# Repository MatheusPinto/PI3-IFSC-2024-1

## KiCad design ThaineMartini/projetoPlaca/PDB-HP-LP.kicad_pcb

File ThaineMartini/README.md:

# <p align="center"> Comandos, Aquisição e Armazenamento de dados de uma bancada de teste de um sistema de energia híbrido para drone </p>

<p class="text-info recuo" align="justify">
O mercado atual de drones, são raras as opções que possuem autonomia de voo maior que 50 minutos, fator esse que pode dificultar ou mesmo inviabilizar a realização de algumas missões. A marca mais conhecida do mercado (DJI) possui apenas uma opção comercial que promete atuar em uma margem maior de tempo que o limiar mencionado. Essa condição existe por conta das limitações de densidade energética dos armazenadores de energia disponíveis no mercado: baterias. Nesse contexto, uma opção viável para aumentar a autonomia consiste na utilização de conjuntos híbridos que podem ser embarcados na aeronave, utilizando um motor à combustão como parte do sistema de geração de energia elétrica.
</p>
<p class="text-info recuo"align="justify">
Para implementar esse conjunto híbrido no drone, uma solução é importar sistemas pré-fabricados de geração de energia de outros países, como a China. Contudo a hipotética fabricação e nacionalização desse subsistema é uma solução interessante, haja vista o potencial de diminuição de custos, possibilidade de personalização da máquina e ausência dos trâmites de importação.
</p>

<p class="text-info recuo"align="justify">
Para realizar esse projeto, foi desenvolvida uma bancada de testes pelo laboratório de drones do Instituto Federal de Ciência e Tecnologia de Santa Catarina (IFSC). O dispositivo consiste em um motor a combustão interna (MCI) acoplado a um motor BrushLess Direct Current (BLDC), que funciona como gerador de energia, e um retificador trifásico conectado à saída do gerador. Nessa configuração, o acelerador do motor à combustão possui um atuador eletromecânico (servo) que pode ser acionado eletronicamente por um sistema microcontrolado, que deve ajustar automaticamente e em tempo real a posição do acelerador conforme a energia demandada na saída o gerador trifásico (BLDC). Um dos principais desafios dessa simulação é desenvolver um sistema eletrônico de monitoramento e controle que mantenha a tensão constante mesmo com a variação da carga. Com o objetivo de desenvolver esse sistema de controle, é necessário projetar e confeccionar uma placa auxiliar que condiciona os sinais aferidos no sistema para um microcontrolador onde são tratados e armazenados em um log. Essa placa será desenvolvida no projeto integrador 3 e será detalhada a seguir.
</p>

<p class="text-info recuo"align="justify">
Esse projeto integrador deve cumprir os seguintes requisitos, aferir e condicionar os sinais de RPM, temperatura do motor a combustão interna (MCI), corrente e tensão no barramento CC (pós-retificador) do sistema. Deve gerar dois sinais de pulse width modulation (PWM), um para o servo motor que acelera o MCI e outro para o driver que movimenta o BLDC para dar partida no motor. Esta placa também deve possuir dois conversores um de 12V e outro de 5V para a alimentação de payload e periféricos do drone. Assim como tem que gerar um arquivo de dados que contenha todos os sinais que foram monitorados. Na Figura 1, está delineado em formato de diagrama o projeto da PCI.
</p>
<div align="center">
Figura 1 - Diagrama do hardware

<figcaption>Fonte: Acervo pessoal</figcaption>
</div>

#### Cronograma idealizado 
<p> 12/03 - Cronograma </p>
<p> 20/03 - Levantamento dos componentes de projeto e pré requisitos </p>
<p> 27/03 - Levantamento dos componentes de projeto e pré requisitos </p>
<p> 03/04 - Esquemático da placa </p>
<p> 10/04 - Esquemático da placa </p>
<p> 17/04 - Layout da placa </p>
<p> 24/04 - Layout da placa </p>
<p> 08/05 - Fabricação da placa, documentação e programação do micro </p>
<p> 15/05 - Fabricação da placa, documentação e programação do micro </p>
<p> 22/05 - 1° TESTE e levantamento de log para análise </p>
<p> 29/05 - Ajustes </p>
<p> 05/06 - 2° TESTE e levantamento de log para análise </p>
<p> 12/06 - Ajustes </p>
<p> 19/06 - Apresentação </p>

## Desenvolvimento

### Componentes
<p> Os componentes foram selecionados de acordo com a disponibilidade no laboratório e com os requisitos o projeto </p>
<p> Servo motor: MG995, a aplicação necessita de um servo robusto e esse componente tem disponível no laboratório </p>
<p> UControlador: F280025C da Texas Instruments, um microcontrolador que aguenta o sistema de controle que será aplicado futuramente </p>
<p> Sensor de corrente: ACS758 150B, o máximo de corrente que o sensor terá que medir é de 80A, o sensor escolhido mede até 150A e tem disponivel no laboratório </p>
<p> Conversor CC/CC 48V - 5V: THL15-4811WL, robusto suficiente para aguentar os picos de tensão (até 60V) e tem disponivel no laboratório </p>
<p> Conversor CC/CC 48V - 12V: EC5SBW-48S12, robusto suficiente para aguentar os picos de tensão (até 60V) e tem disponivel no laboratório </p>
<p> Sensor de temperatura: NTC 33950 100k, o sensor deve medir pelo menos de 10 C até 200 C, o sensor escolhido mede de -4 a 270 C </p>
<p> Amplificador Opercional: TLV 9044 DIR, escolhido pela disponibilidade no laboratório </p>
<p> Regulador de Tensão: LM 1117 </p>

### Projeto
<p align="justify"> O projeto foi realizado de acordo com diagrama de blocos demonstrado anteriormente</p>

#### Leitura da corrente

<p align="justify">O circuito utilizado para a leitura da corrento envolve o sensor (ACS 758B), o condicionamento de sinal e um filtro ativo passa-baixa (Sallen-Key). Para a adequar os niveis de tensão foi utilizado um circuito subtrator, descrito abaixo </p>

<picture>
 
</picture>

<p align="justify">Para a tensão V1 maxima, levamos em consideração que quando a corrente é nula a tensão de saída do ACS vai ser Vcc/2 = 1.65.</p>
<p align="justify">Para a tensão V1 minima, levamos em consideração que quando a corrente é maxima a tensão de saída do ACS vai ser (Vcc/2) + (Corrente maxima * sensibilidade do sensor), a sensibilidade do sensor pelo datasheet é 13*10^-3 e a corrente  maxima prevista é 100 A (com uma certa sobra por precaução), com isso temos V2 = 2.95 </p>
<p align="justify">Para V2 é utilizado um divisor resistivo para conseguir a tensão de 1.5V (R1 = 1.2k ohm e R2=1k ohm).  </p>

<picture>
 
</picture>

#### Leitura da tensão 
<p align="justify"> Para a leitura da Tensão foi usado um divisor resistivo de tensão juntamente com um filtro Sallen-Key de segunda ordem (passa-baixa) para a diminuição de ruido na leitura do sinal. Para calcular o divisor resistivo foi assumindo que R1 = 56560 ohm (dividido em dois resistores um de 56k ohm e outro e 560 ohm), R2=3k3 ohm e com uma tensão maxima de 60V. Para o calculo do filtro Sallen-Key, foi previsto pelos professores do laboratori de dornes uma frequência de corte de 723 Hz para o filtro, para a definição dos capacitores e resistores foi utilizada a formula fc = 1/(2*pi*sqrt(R1*C1*R2*C2)) onde ao definir C1 e C2 com 100 nF, temos R1 e R2 de 2k2 ohm. O esquemático é mostrado na figura abaixo. </p>

<picture>
 
</picture>

### Esquemático 
<p align="justify">Através do software KiCad e com os requisitos levantados anteriormente foi realizado a implementação do esquemático (pdf com o esquemático completo na pasta do projeto), que é composto por 5 Blocos principais: </p>
<p> - Alimentação: O bloco de alimentação é formado pela conexão da Bateria de 12S (aproximadamente 48V) e a conexão do Gerador Elétrico</p>
<p> - Potência: Possui dois conversores THL15-4811WL (para 5V) e o EC5SBW-48S12 (para 12V), com o circuito sugerido na folha de dados</p>
<p> - Conexões: São as conexões que a placa possui com o meio esterno, primeramente o 4 conectores XT60 que são usados para a conectar a carga (para testes inicias uma carga resistiva), 3 conectores JST-XH de duas vias, um para a alimentação da bomba que auxilia no resfriamento o motor, outro para aferir a temperatura e por último para a ignição do motor, 6 conectores JST-XH de 3 vias sendo, para o esc que vai acionar o BLDC para dar a partida no motor a combustão, para o servo motor que auxilia no controle, um que recebe um pulso da controladora de voo para o acionamento remoto do motor, e dois reservas caso venha a precisar no futuro, alem desses conectores temos nesse bloco um optacoplador para proteção do circuito com o sinal que vem do tacomêtro, um jumper para a alimentação do F280025C caso precise debugar o circuito no computador, um modulo para leitura do cartão SD e dois leds para informações. Para a comunicação com a controladora de voo foi prevista duas conexões, uma por JST-XH  e uma por JST-GH, para conseguir utilizar os dois tipos de controlaora disponiveis no laboratório (cube orange e pixhalk)</p>
<p> - Condicionamento do Sinal: Contendo dois sinais que precisam ser ajustados para a leitura no F280025C a tensão que passa por um divisor resistivo para diminuir a tensão, um buffer e um filtro Sallen-Key e a corrente que após passar por um sensor de efeito hall (ACS758) passa por um buffer, um circuito somador para amplificar a tensão fornecida pelo sensor e um filtro sallen-key, o detalhemento desses dois circuitos está fornecido na folha de calculos.</p>

### Layout
<p>O layout seguiu os seguintes requisitos:</p>
  <p>- Deixar todos os componentes na parte superior da placa assim como os pontos de medição de tensão</p>
  <p>- A parte de potência separada e com menor interatividade com o resto da placa</p>
  <p>- Conectores na borda da placa </p>
  <p>- Malha de potência no barramento (no bloco de alimentação) </p>
  <p align="justify">Os requisitos foram pensados para evitar ruídos indesejados, evitar que a placa sobreaqueça, melhor conexão dos perifericos e para que acaso haja algum problema no futuro seja fácil de encontrar o que está gerando.</p>
### Programação

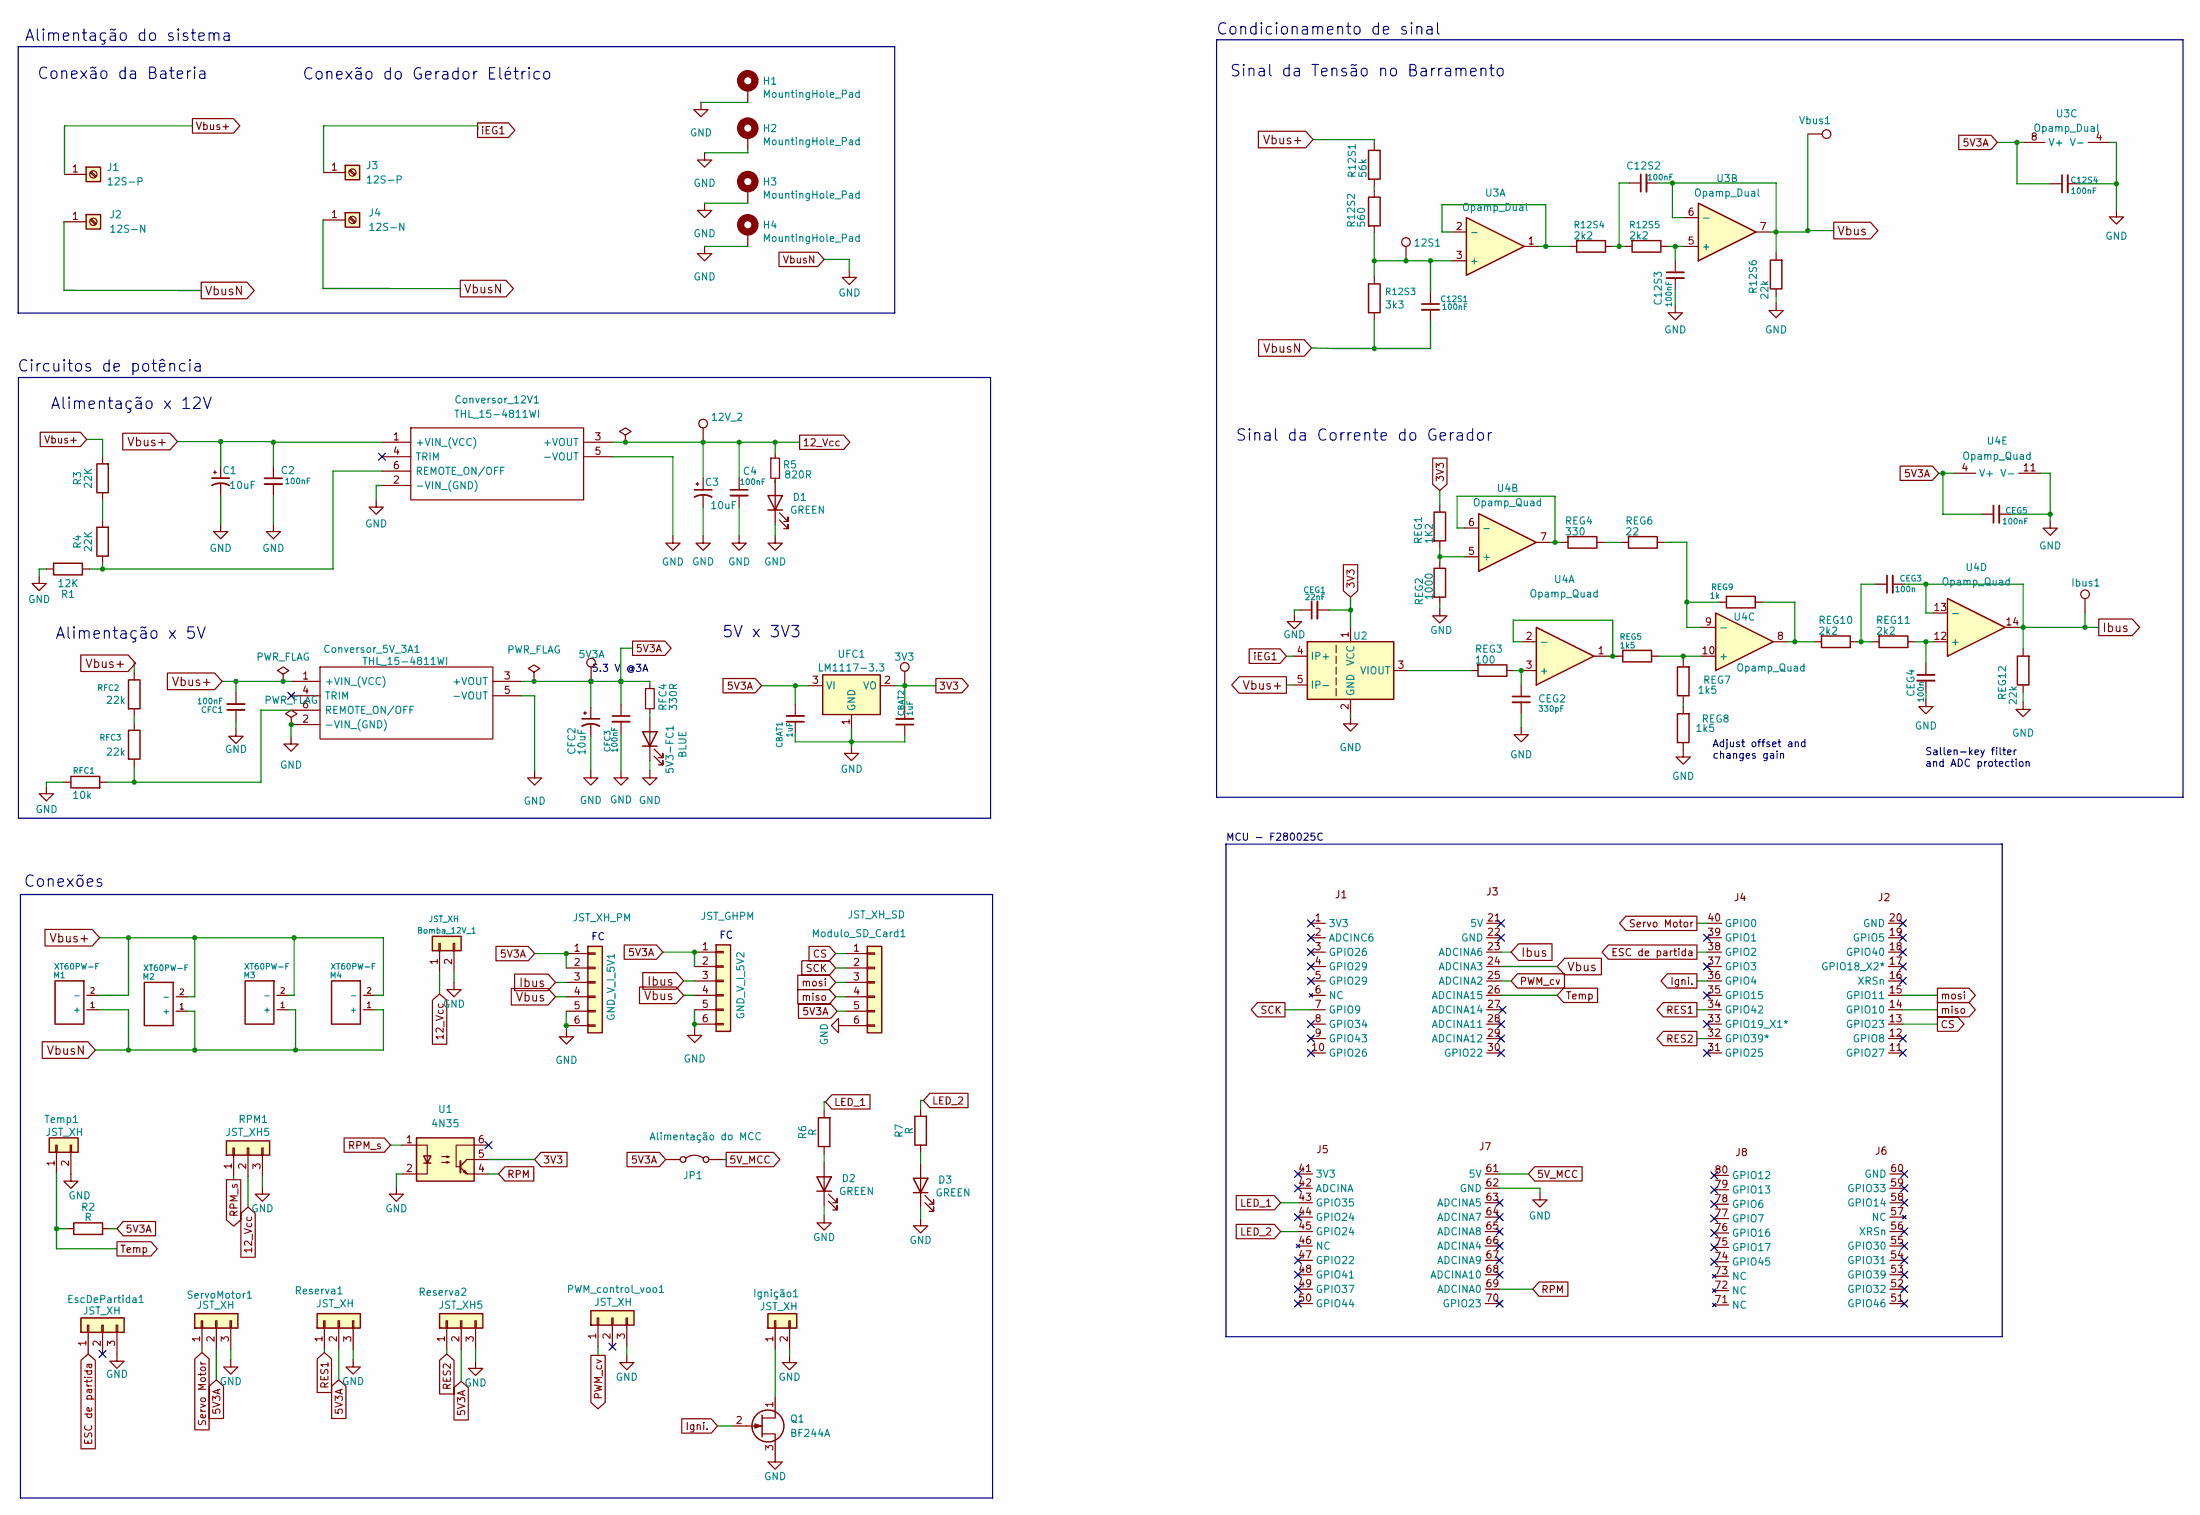
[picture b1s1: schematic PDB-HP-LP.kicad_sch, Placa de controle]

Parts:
5V3-FC1: BLUE; LED_0805_2012Metric
5V3A1: 5V3A; tp
5V3A2: 3V3; tp
12S1: TestPoint; tp
12V_1: 12V_2; tp
Bomba_12V_1: JST_XH; Hirose_DF13-02P-1.25DSA_1x02_P1.25mm_Vertical
C1, C3: 10uF; CP_Elec_6.3x5.4
C2: 100nF; C_Rect_L16.5mm_W6.0mm_P15.00mm_MKT
C4: 100nF; C_0805_2012Metric
C12S1, C12S2, C12S3, C12S4: 100nF; C_0805_2012Metric_Pad1.18x1.45mm_HandSolder
CBAT1, CBAT2: 1uF; C_0805_2012Metric_Pad1.18x1.45mm_HandSolder
CEG1: 22nF; C_0805_2012Metric_Pad1.18x1.45mm_HandSolder
CEG2: 330pF; C_0805_2012Metric_Pad1.18x1.45mm_HandSolder
CEG3, CEG4: 100n; C_0805_2012Metric_Pad1.18x1.45mm_HandSolder
CEG5: 100nF; C_0805_2012Metric_Pad1.18x1.45mm_HandSolder
CFC1: 100nF; C_Rect_L13.0mm_W4.0mm_P10.00mm_FKS3_FKP3_MKS4
CFC2: 10uF; CP_Elec_6.3x5.4
CFC3: 100nF; C_0805_2012Metric_Pad1.18x1.45mm_HandSolder
Conversor_5V_3A1, Conversor_12V1: THL_15-4811WI; THL154811WI; Manufacturer_Part_Number THL 15-4811WI; Mouser Part Number 495-THL15-4811WI
D1, D2, D3: GREEN; LED_0805_2012Metric
EscDePartida1: JST_XH; Hirose_DF13-03P-1.25DSA_1x03_P1.25mm_Vertical
GND_V_I_5V1: JST_XH_PM; Hirose_DF13-06P-1.25DSA_1x06_P1.25mm_Vertical
GND_V_I_5V2: JST_GHPM; BM06BGHSTBTLFSN
H1, H2, H3, H4: MountingHole_Pad; MountingHole_3.5mm_Pad_Via
Ibus1: TestPoint; tp
Ignição1: JST_XH; Hirose_DF13-02P-1.25DSA_1x02_P1.25mm_Vertical
J1, J3: 12S-P; IFSC_TERMINAL_SCREW
J2, J4: 12S-N; IFSC_TERMINAL_SCREW
JP1: Alimentação do MCC; PinHeader_1x02_P2.54mm_Vertical
M1, M2, M3, M4: XT60PW-F; AMASS_XT60PW-M
MCU1: F280025C; LAUNCHXLF280025C
Modulo_SD_Card1: JST_XH_SD; Hirose_DF13-06P-1.25DSA_1x06_P1.25mm_Vertical
PWM_control_voo1: JST_XH; Hirose_DF13-03P-1.25DSA_1x03_P1.25mm_Vertical
Q1: BF244A; TO-92_Inline
R1: 12K; R_0805_2012Metric_Pad1.20x1.40mm_HandSolder
R2, R6, R7: R; R_0805_2012Metric_Pad1.20x1.40mm_HandSolder
R3, R4: 22K; R_0805_2012Metric_Pad1.20x1.40mm_HandSolder
R5: 820R; R_0805_2012Metric_Pad1.20x1.40mm_HandSolder
R12S1: 56k; R_0805_2012Metric_Pad1.20x1.40mm_HandSolder
R12S2: 560; R_0805_2012Metric_Pad1.20x1.40mm_HandSolder
R12S3: 3k3; R_0805_2012Metric_Pad1.20x1.40mm_HandSolder
R12S4, R12S5: 2k2; R_0805_2012Metric_Pad1.20x1.40mm_HandSolder
R12S6: 22k; R_0805_2012Metric_Pad1.20x1.40mm_HandSolder
REG1: 1K2; R_0805_2012Metric_Pad1.20x1.40mm_HandSolder
REG2: 1000; R_0805_2012Metric_Pad1.20x1.40mm_HandSolder
REG3: 100; R_0805_2012Metric_Pad1.20x1.40mm_HandSolder
REG4: 330; R_0805_2012Metric_Pad1.20x1.40mm_HandSolder
REG5, REG7, REG8: 1k5; R_0805_2012Metric_Pad1.20x1.40mm_HandSolder
REG6: 22; R_0805_2012Metric_Pad1.20x1.40mm_HandSolder
REG9: 1k; R_0805_2012Metric_Pad1.20x1.40mm_HandSolder
REG10, REG11: 2k2; R_0805_2012Metric_Pad1.20x1.40mm_HandSolder
REG12: 22k; R_0805_2012Metric_Pad1.20x1.40mm_HandSolder
RFC1: 10k; R_0805_2012Metric_Pad1.20x1.40mm_HandSolder
RFC2, RFC3: 22k; R_0805_2012Metric_Pad1.20x1.40mm_HandSolder
RFC4: 330R; R_0805_2012Metric_Pad1.20x1.40mm_HandSolder
RPM1: JST_XH5; Hirose_DF13-03P-1.25DSA_1x03_P1.25mm_Vertical
Reserva1: JST_XH; Hirose_DF13-03P-1.25DSA_1x03_P1.25mm_Vertical
Reserva2: JST_XH5; Hirose_DF13-03P-1.25DSA_1x03_P1.25mm_Vertical
ServoMotor1: JST_XH; Hirose_DF13-03P-1.25DSA_1x03_P1.25mm_Vertical
Temp1: JST_XH; Hirose_DF13-02P-1.25DSA_1x02_P1.25mm_Vertical
U1: 4N35; DIP-6_W7.62mm
U2: ACS759xCB-150B-PFF; Allegro_CB_PFF
U3: Opamp_Dual; SOIC127P600X175-8N
U4: Opamp_Quad; SOIC-14_3.9x8.7mm_P1.27mm
UFC1: LM1117-3.3; SOT-223-3_TabPin2
Vbus1: TestPoint; tp

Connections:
3V3: 5V3A2.1, CBAT2.2, CEG1.2, REG1.1, U1.5, U2.1 (VCC), UFC1.2 (VO)
5V3A: 5V3A1.1, C12S4.1, CBAT1.2, CEG5.1, CFC2.1, CFC3.1, Conversor_5V_3A1.3 (+VOUT), GND_V_I_5V1.1, GND_V_I_5V1.2, GND_V_I_5V2.1, GND_V_I_5V2.2, JP1.1 (A), Modulo_SD_Card1.5, R2.2, RFC4.1, Reserva1.2, Reserva2.2, ServoMotor1.2, U3.8 (V+), U4.4 (V+), UFC1.3 (VI); also elsewhere on the board
5V_MCC: JP1.2 (B), MCU1.61 (5V)
12_Vcc: 12V_1.1, Bomba_12V_1.1, C3.1, C4.1, Conversor_12V1.3 (+VOUT), R5.1, RPM1.2
CS: MCU1.13 (GPIO23), Modulo_SD_Card1.1
ESC de partida: EscDePartida1.1, MCU1.38 (GPIO2)
Ibus: CEG3.2, GND_V_I_5V1.3, GND_V_I_5V2.3, Ibus1.1, MCU1.23 (ADCINA6), REG12.2, U4.13 (-), U4.14; also elsewhere on the board
Igni.: MCU1.36 (GPIO4), Q1.2 (G)
LED_1: MCU1.43 (GPIO35), R6.2
LED_2: MCU1.45 (GPIO24), R7.2
unnamed: 5V3-FC1.2 (A), RFC4.2
unnamed: C12S2.1, R12S4.1, R12S5.2
unnamed: CEG3.1, REG10.1, REG11.2
unnamed: Conversor_5V_3A1.6 (REMOTE_ON/OFF), RFC1.2, RFC3.2
unnamed: Conversor_12V1.6 (REMOTE_ON/OFF), R1.1, R4.1
unnamed: D1.2 (A), R5.2
unnamed: D2.2 (A), R6.1
unnamed: D3.2 (A), R7.1
unnamed: Ignição1.1, Q1.1 (D)
unnamed: R3.1, R4.2
unnamed: R12S1.2, R12S2.1
unnamed: REG4.1, REG6.2
unnamed: REG7.1, REG8.2
unnamed: REG9.1, REG10.2, U4.8
unnamed: RFC2.2, RFC3.1
unnamed: REG3.2, U2.3 (VIOUT)
unnamed: 12S1.1, C12S1.1, R12S2.2, R12S3.1, U3.3 (+)
unnamed: R12S4.2, U3.1, U3.2 (-)
unnamed: C12S3.1, R12S5.1, U3.5 (+)
unnamed: CEG2.1, REG3.1, U4.3 (+)
unnamed: REG5.2, U4.1, U4.2 (-)
unnamed: REG1.2, REG2.1, U4.5 (+)
unnamed: REG4.2, U4.6 (-), U4.7
unnamed: REG5.1, REG7.2, U4.10 (+)
unnamed: REG6.1, REG9.2, U4.9 (-)
unnamed: CEG4.1, REG11.1, U4.12 (+)
PWM_cv: MCU1.25 (ADCINA2), PWM_control_voo1.1
RES1: MCU1.34 (GPIO42), Reserva1.1
RES2: MCU1.32 (GPIO39*), Reserva2.1
RPM: MCU1.69 (ADCINA0), U1.4
RPM_s: RPM1.1, U1.1
SCK: MCU1.7 (GPIO9), Modulo_SD_Card1.2
Servo Motor: MCU1.40 (GPIO0), ServoMotor1.1
Temp: MCU1.26 (ADCINA15), R2.1, Temp1.1
Vbus: C12S2.2, GND_V_I_5V1.4, GND_V_I_5V2.4, MCU1.24 (ADCINA3), R12S6.2, U3.6 (-), U3.7, Vbus1.1; also elsewhere on the board
Vbus+: C1.1, C2.1, CFC1.2, Conversor_5V_3A1.1 (+VIN_(VCC)), Conversor_12V1.1 (+VIN_(VCC)), J1.1, M1.2 (-), M2.2 (-), M3.2 (-), M4.2 (-), R3.2, R12S1.1, RFC2.1, U2.5 (IP-); also elsewhere on the board
VbusN: 5V3-FC1.1 (K), Bomba_12V_1.2, C1.2, C2.2, C3.2, C4.2, C12S1.2, C12S3.2, C12S4.2, CBAT1.1, CBAT2.1, CEG1.1, CEG2.2, CEG4.2, CEG5.2, CFC1.1, CFC2.2, CFC3.2, Conversor_5V_3A1.2 (-VIN_(GND)), Conversor_5V_3A1.5 (-VOUT), Conversor_12V1.2 (-VIN_(GND)), Conversor_12V1.5 (-VOUT), D1.1 (K), D2.1 (K), D3.1 (K), EscDePartida1.3, GND_V_I_5V1.5, GND_V_I_5V1.6, GND_V_I_5V2.5, GND_V_I_5V2.6, H1.1, H2.1, H3.1, H4.1, Ignição1.2, J2.1, J4.1, M1.1 (+), M2.1 (+), M3.1 (+), M4.1 (+), MCU1.62 (GND), Modulo_SD_Card1.6, PWM_control_voo1.3, Q1.3 (S), R1.2, R12S3.2, R12S6.1, REG2.2, REG8.1, REG12.1, RFC1.1, RPM1.3, Reserva1.3, Reserva2.3, ServoMotor1.3, Temp1.2, U1.2, U2.2 (GND), U3.4 (V-), U4.11 (V-), UFC1.1 (GND); also elsewhere on the board
iEG1: J3.1, U2.4 (IP+)
miso: MCU1.14 (GPIO10), Modulo_SD_Card1.4
mosi: MCU1.15 (GPIO11), Modulo_SD_Card1.3

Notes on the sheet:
Sinal da Tensão no Barramento
Conexões
Alimentação x 12V
Sinal da Corrente do Gerador
MCU - F280025C
Conexão da Bateria
Sallen-key filter and ADC protection
Adjust offset and changes gain
Conexão do Gerador Elétrico
Condicionamento de sinal
5.3 V @3A
Circuitos de potência
5V x 3V3
Alimentação do sistema
Alimentação x 5V

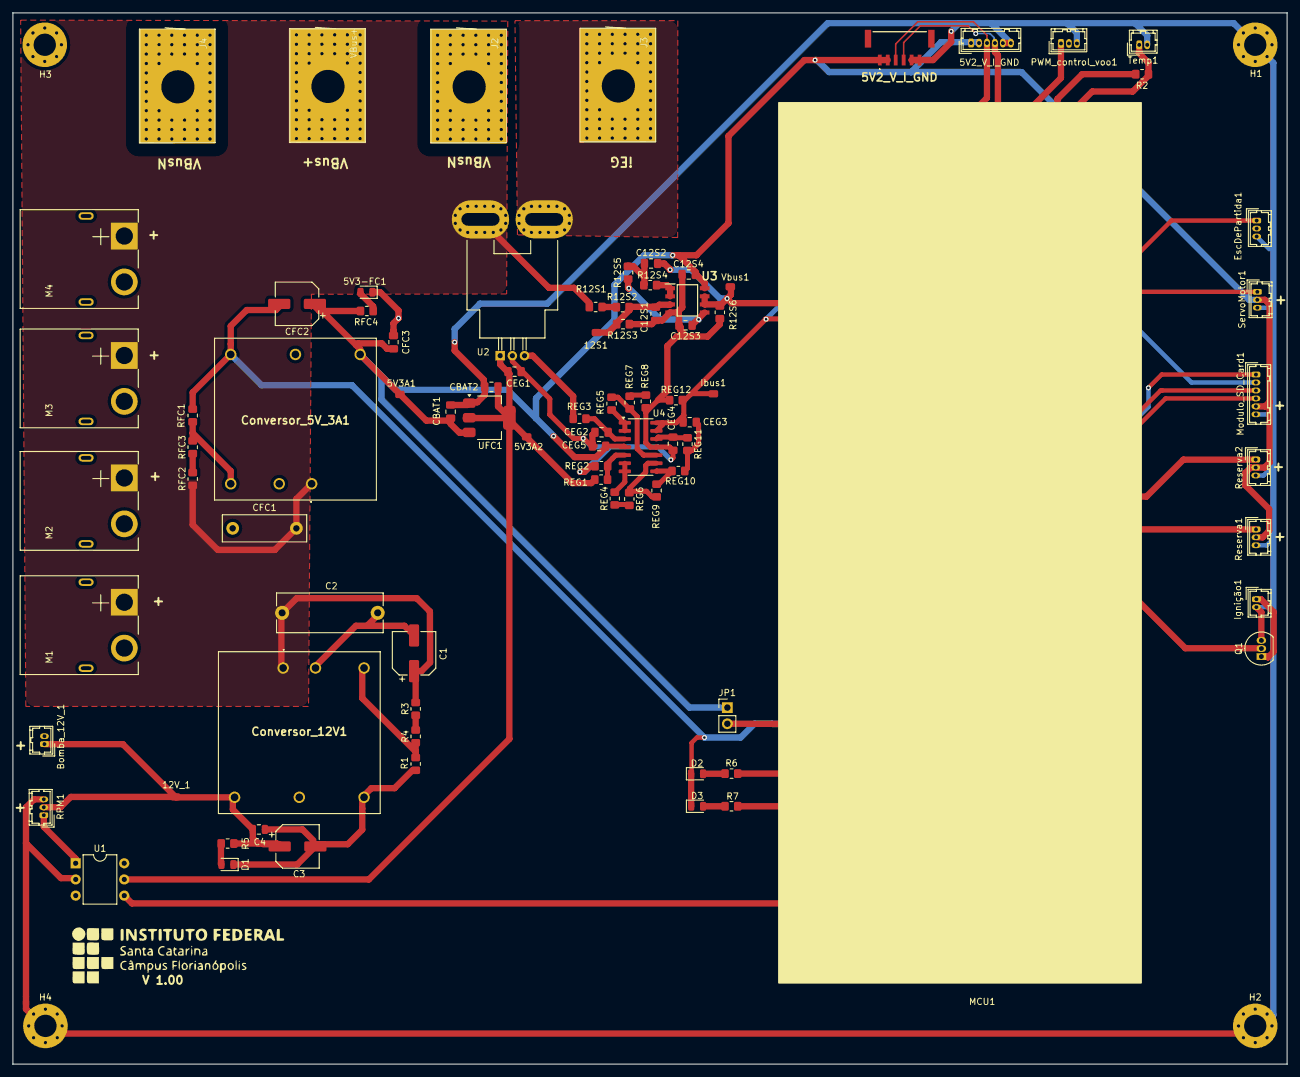
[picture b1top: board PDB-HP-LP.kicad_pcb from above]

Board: 2 copper layers, 200.0 x 165.0 mm, 91 parts (0 on the bottom side), 50 nets.

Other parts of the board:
5V2_V_I_GND: JST_GHPM; BM06BGHSTBTLFSN
5V2_V_I_GND#2: JST_XH_PM; Hirose_DF13-06P-1.25DSA_1x06_P1.25mm_Vertical
VBus+: 12S-P; IFSC_TERMINAL_SCREW

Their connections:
5V3A: 5V2_V_I_GND.1, 5V2_V_I_GND.2, 5V2_V_I_GND#2.1, 5V2_V_I_GND#2.2; also elsewhere on the board
Ibus: 5V2_V_I_GND.3, 5V2_V_I_GND#2.3; also elsewhere on the board
Vbus: 5V2_V_I_GND.4, 5V2_V_I_GND#2.4; also elsewhere on the board
Vbus+: VBus+.1; also elsewhere on the board
VbusN: 5V2_V_I_GND.5, 5V2_V_I_GND.6, 5V2_V_I_GND#2.5, 5V2_V_I_GND#2.6; also elsewhere on the board

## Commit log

2024-04-27 update readme with project information
2024-08-14 simplifica a maquina de estados e adiciona funcionalidades
2024-08-14 Adiciona arquivos para utilização no Atmel(Microchip)Studio
2024-08-14 Bug fix + test
2024-08-14 Update TODO.MD
    Substitui a parte de medição da corrente por medição da tensão
    Marca alguns itens como feitos
    Detalha outros itens
2024-08-14 adicionando o readme
2024-08-21 Update Resultados.md
    Teste eletrodos
2024-08-26 inserindo imagens do app
2024-08-26 adiciona teste de ADC para facilitar prototipagem
2024-08-28 reorganização das pastas e adição dos arquivos finais
2024-08-28 limpa arquivos de teste e adiciona leitura de corrente
2024-08-28 ajustes na interface
2024-09-03 Create README.md
    Criação do README.md
2024-09-03 Create .gitignore
    adicionar pasta images
2024-09-03 modularização na maquina de estados
2024-09-03 Update README.md
    Atualização de estrutura de tópicos
2024-09-03 Add files via upload
    Adicionar imagens da especificações das telas
2024-09-03 Update README.md
    correção do link para as imagens das telas
2024-09-03 Update README.md
    correção do indice
2024-09-03 Update README.md
    corrigidas referencias para monitor e moldura
2024-09-03 Add files via upload
    adicionando fotos
2024-09-04 testes finais
2024-09-04 Update README.md
    adicionando informações de componentes
2024-09-04 Add files via upload
    add imagens de componentes
2024-09-04 Update README.md
    adicionado link de telas implementadas
2024-09-04 Add files via upload
    adicionando novas imagens
2024-09-04 add new modules version and config core file updated to the last version
2024-09-04 Update README.md
    otimizado proporção/ocupação de algumas imagens
2024-09-04 removing modules broken and conflictants
2024-09-04 add broken modules with no issues
2024-09-04 Update README.md
    adicionando opinião sobre passos futuros
2024-09-04 Add files via upload
    adicionar foto
2024-09-04 Update README.md
    adicionando visão geral
2024-09-04 Add files via upload
    Adicionando imagens
2024-09-05 CRUD de operações com o banco de dados
2024-09-05 Renomear pasta de código da balança
2024-09-05 Adicionar código para funcionamento da balança
2024-09-05 Adicionar script para conexão com banco de dados no AWS
2024-09-05 Adicionar bibliotecas necessárias do projeto
2024-09-05 Adicionar script de funções de utilidade do projeto
2024-09-05 Adicionar arquivo com pesos do yolov8
2024-09-05 Adicionar script para popular tabela de alimentos no DB do AWS
2024-09-05 Adicionar main.py do projeto
2024-09-05 ajustes de PWM
2024-09-06 Adicionar documentação do projeto
2024-09-06 Adicionar no readme texto sobre o requirements.txt
2024-09-06 Remover breakpoint de script rename_image_files.py
2024-09-06 Adicionar docstrings para CRUD de usuários
2024-09-06 Adicionar docstrings para métodos em CRUD dos alimentos
2024-09-06 ajuste pwm do motor, pequenos bugs
2024-09-07 reduzi a qualidade para o git aceitar os videos
2024-09-07 Adicionados informações de testes
2024-09-07 new photos
2024-09-07 update photos
2024-09-07 tópico 3
2024-09-07 atualização dos tópicos e imagens
2024-09-09 topicos 9 e 10
